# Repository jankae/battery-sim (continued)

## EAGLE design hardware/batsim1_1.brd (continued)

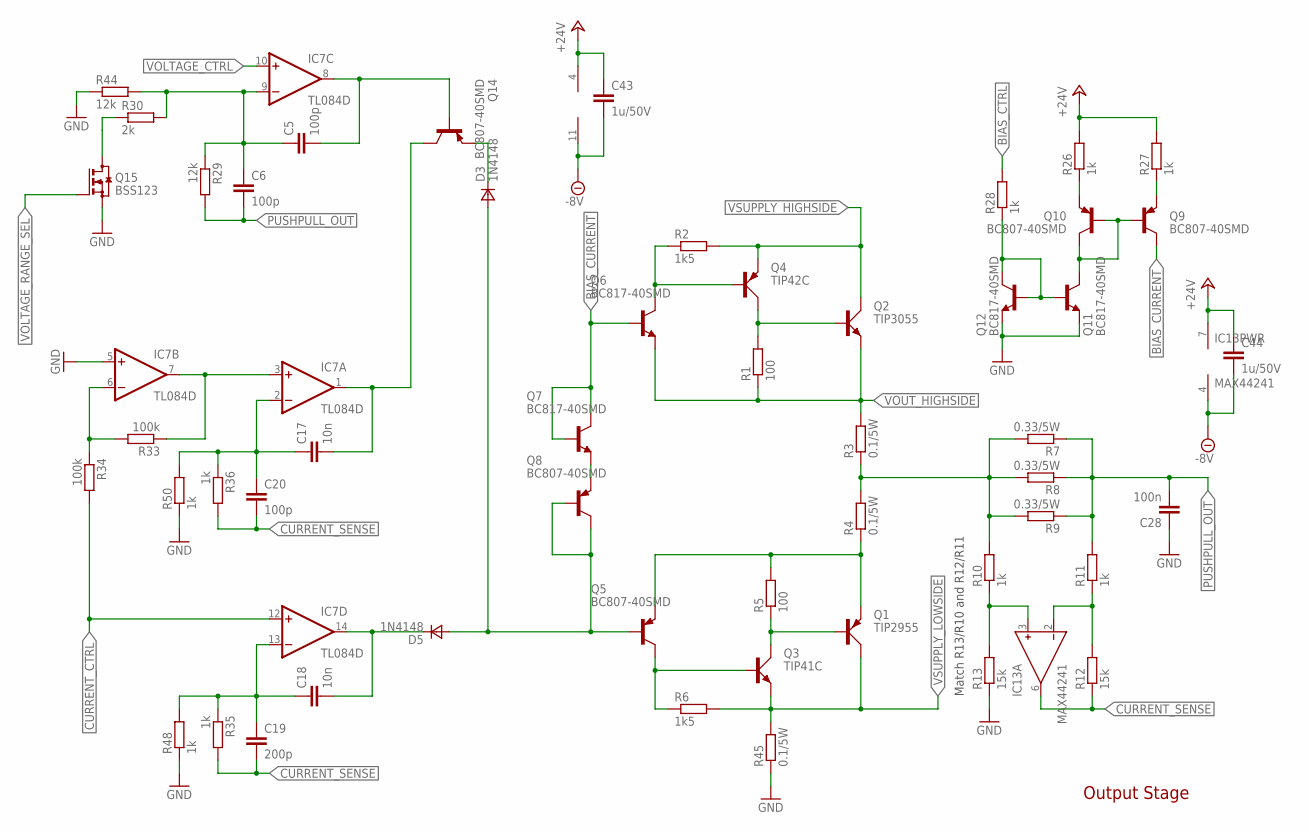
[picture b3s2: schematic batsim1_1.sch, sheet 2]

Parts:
C5, C6, C20: 100p; C0603
C17, C18: 10n; C0603
C19: 200p; C0603
C28: 100n; C1206
C43, C44: 1u/50V; C0603
D3, D5: 1N4148; SOD323
IC7: TL084D; SO14
IC13: MAX44241; UMAX8
Q1: TIP2955; TOP3AV
Q2: TIP3055; TOP3AV
Q3: TIP41C; TO220AV
Q4: TIP42C; TO220AV
Q5, Q8, Q9, Q10, Q14: BC807-40SMD; SOT23-BEC
Q6, Q7, Q11, Q12: BC817-40SMD; SOT23-BEC
Q15: BSS123; SOT23
R1, R5: 100; R0603
R2, R6: 1k5; R0603
R3, R4, R45: 0.1/5W; 5WAXIAL
R7, R8, R9: 0.33/5W; 5WAXIAL
R10, R11, R26, R27, R28, R35, R36, R48, R50: 1k; R0603
R12, R13: 15k; R0603
R29, R44: 12k; R0603
R30: 2k; R0603
R33, R34: 100k; R0603

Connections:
+24V: C43.1, C44.1, IC7.4 (V+), IC13.7 (V+), R26.2, R27.2; also elsewhere on the board
-8V: C43.2, C44.2, IC7.11 (V-), IC13.4 (V-); also elsewhere on the board
BIAS_CTRL: R28.2; also elsewhere on the board
BIAS_CURRENT: Q6.B, Q7.B, Q7.C, Q9.C
CURRENT_CTRL: IC7.12 (+IN), R34.2; also elsewhere on the board
CURRENT_SENSE: C19.2, C20.2, IC13.6 (OUT), R12.1, R35.2, R36.2; also elsewhere on the board
GND: C28.1, IC7.5 (+IN), Q11.E, Q12.E, Q15.2 (S), R13.1, R44.1, R45.1, R48.1, R50.1; also elsewhere on the board
unnamed: Q15.3 (D), R30.1
unnamed: Q2.B, Q4.C, R1.2
unnamed: Q4.B, Q6.C, R2.1
unnamed: R3.1, R4.2, R7.2, R8.2, R9.2, R10.2
unnamed: Q1.E, Q5.E, R4.1, R5.2
unnamed: Q1.B, Q3.C, R5.1
unnamed: Q3.B, Q5.C, R6.1
unnamed: Q7.E, Q8.E
unnamed: D3.1 (C), Q14.E
unnamed: IC13.3 (IN+), R10.1, R13.2
unnamed: IC13.2 (IN-), R11.1, R12.2
unnamed: Q9.B, Q10.B, Q10.C, Q11.C
unnamed: Q11.B, Q12.B, Q12.C, R28.1
unnamed: Q10.E, R26.1
unnamed: Q9.E, R27.1
unnamed: C5.2, IC7.8 (OUT), Q14.B
unnamed: IC7.6 (-IN), R33.2, R34.1
unnamed: IC7.3 (+IN), IC7.7 (OUT), R33.1
unnamed: C18.2, D5.1 (C), IC7.14 (OUT)
unnamed: C18.1, C19.1, IC7.13 (-IN), R35.1, R48.2
unnamed: C17.2, IC7.1 (OUT), Q14.C
unnamed: C17.1, C20.1, IC7.2 (-IN), R36.1, R50.2
PUSHPULL_CTRL: D3.2 (A), D5.2 (A), Q5.B, Q8.B, Q8.C
PUSHPULL_OUT: C6.2, C28.2, R7.1, R8.1, R9.1, R11.2, R29.2; also elsewhere on the board
VOLTAGE_CTRL: IC7.10 (+IN); also elsewhere on the board
VOLTAGE_FEEDBACK: C5.1, C6.1, IC7.9 (-IN), R29.1, R30.2, R44.2
VOLTAGE_RANGE_SEL: Q15.1 (G); also elsewhere on the board
VOUT_HIGHSIDE: Q2.E, Q6.E, R1.1, R3.2; also elsewhere on the board
VSUPPLY_HIGHSIDE: Q2.C, Q4.E, R2.2; also elsewhere on the board
VSUPPLY_LOWSIDE: Q1.C, Q3.E, R6.2, R45.2; also elsewhere on the board

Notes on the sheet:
Match R13/R10 and R12/R11
Output Stage

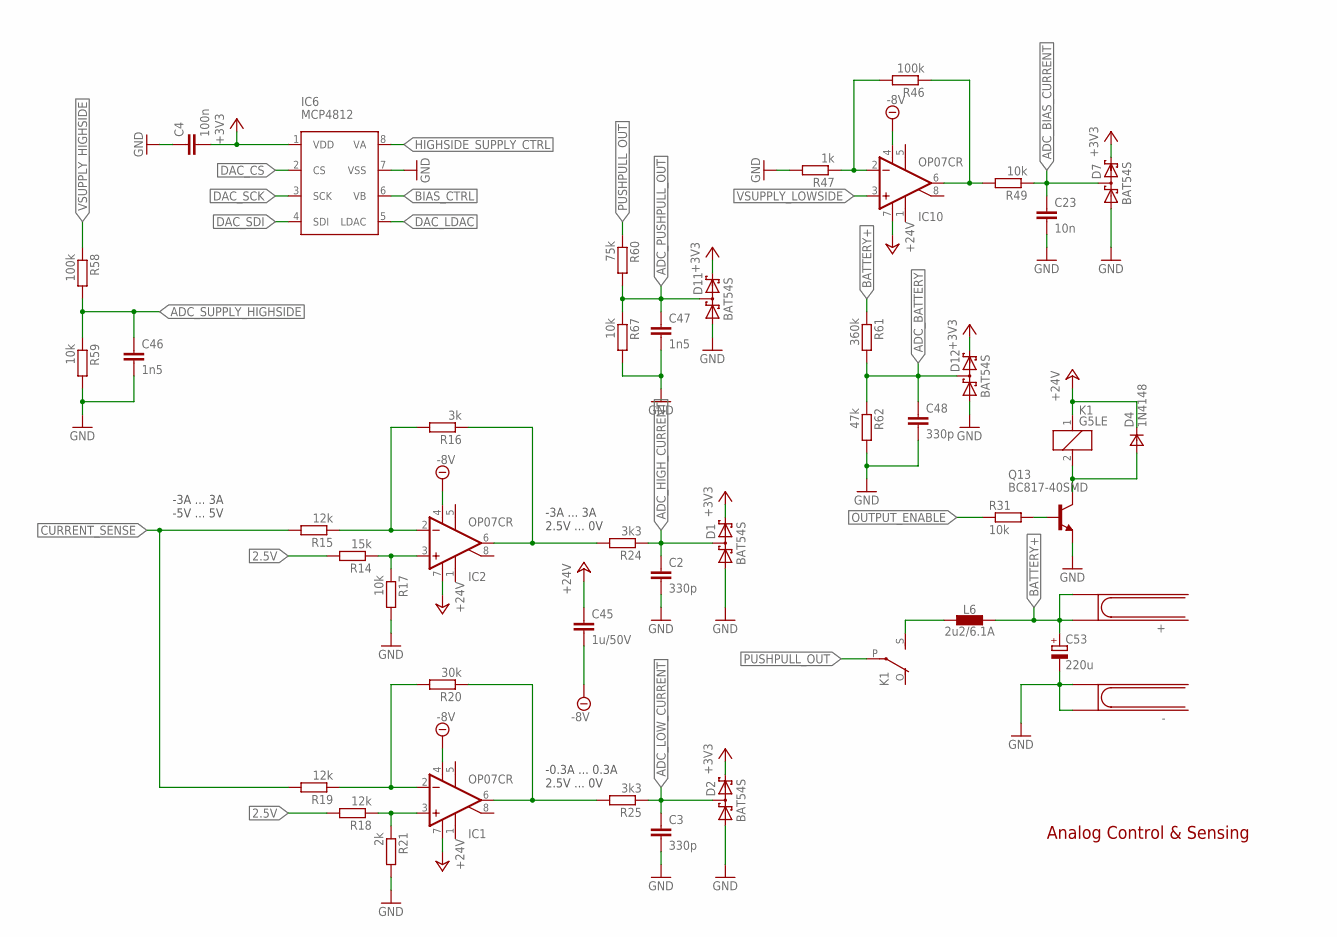
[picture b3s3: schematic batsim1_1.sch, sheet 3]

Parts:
+: 4MMJACK
-: 4MMJACK
C2, C3, C48: 330p; C0603
C4: 100n; C0603
C23: 10n; C0603
C45: 1u/50V; C0603
C46, C47: 1n5; C0603
C53: 220u; E5-10,5
D1, D2, D7, D11, D12: BAT54S; SOT23
D4: 1N4148; SOD323
IC1, IC2, IC10: OP07CR; SO08
IC6: MCP4812; SO08
K1: G5LE
L6: 2u2/6.1A; L_NR60XX
Q13: BC817-40SMD; SOT23-BEC
R14: 15k; R0603
R15, R18, R19: 12k; R0603
R16: 3k; R0603
R17, R31, R49, R59, R67: 10k; R0603
R20: 30k; R0603
R21: 2k; R0603
R24, R25: 3k3; R0603
R46, R58: 100k; R0603
R47: 1k; R0603
R60: 75k; R0603
R61: 360k; R0603
R62: 47k; R0603

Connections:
2.5V: R14.2, R18.2; also elsewhere on the board
+3V3: C4.2, D1.2 (C2), D2.2 (C2), D7.2 (C2), D11.2 (C2), D12.2 (C2), IC6.1 (VDD); also elsewhere on the board
+24V: C45.1, D4.1 (C), IC1.7 (V+), IC2.7 (V+), IC10.7 (V+), K1.1; also elsewhere on the board
-8V: C45.2, IC1.4 (V-), IC2.4 (V-), IC10.4 (V-); also elsewhere on the board
ADC_BATTERY: C48.1, D12.3 (C1A2), R61.2, R62.1; also elsewhere on the board
ADC_BIAS_CURRENT: C23.1, D7.3 (C1A2), R49.1; also elsewhere on the board
ADC_HIGH_CURRENT: C2.1, D1.3 (C1A2), R24.1; also elsewhere on the board
ADC_LOW_CURRENT: C3.1, D2.3 (C1A2), R25.1; also elsewhere on the board
ADC_PUSHPULL_OUT: C47.1, D11.3 (C1A2), R60.2, R67.1; also elsewhere on the board
ADC_SUPPLY_HIGHSIDE: C46.1, R58.2, R59.1; also elsewhere on the board
BATTERY+: +.1@1 (1), +.1@2 (2), C53.+, L6.2, R61.1
BIAS_CTRL: IC6.6 (VB); also elsewhere on the board
CURRENT_SENSE: R15.2, R19.2; also elsewhere on the board
DAC_CS: IC6.2 (CS); also elsewhere on the board
DAC_LDAC: IC6.5 (LDAC); also elsewhere on the board
DAC_SCK: IC6.3 (SCK); also elsewhere on the board
DAC_SDI: IC6.4 (SDI); also elsewhere on the board
GND: -.1@1 (1), -.1@2 (2), C2.2, C3.2, C4.1, C23.2, C46.2, C47.2, C48.2, C53.-, D1.1 (A1), D2.1 (A1), D7.1 (A1), D11.1 (A1), D12.1 (A1), IC6.7 (VSS), Q13.E, R17.2, R21.2, R47.2, R59.2, R62.2, R67.2; also elsewhere on the board
HIGHSIDE_SUPPLY_CTRL: IC6.8 (VA); also elsewhere on the board
unnamed: IC10.2 (-IN), R46.2, R47.1
unnamed: IC10.6 (OUT), R46.1, R49.2
unnamed: D4.2 (A), K1.2, Q13.C
unnamed: IC2.3 (+IN), R14.1, R17.1
unnamed: IC2.2 (-IN), R15.1, R16.2
unnamed: IC2.6 (OUT), R16.1, R24.2
unnamed: IC1.3 (+IN), R18.1, R21.1
unnamed: IC1.2 (-IN), R19.1, R20.2
unnamed: IC1.6 (OUT), R20.1, R25.2
unnamed: Q13.B, R31.2
unnamed: K1.S, L6.1
OUTPUT_ENABLE: R31.1; also elsewhere on the board
PUSHPULL_OUT: K1.P, R60.1; also elsewhere on the board
VSUPPLY_HIGHSIDE: R58.1; also elsewhere on the board
VSUPPLY_LOWSIDE: IC10.3 (+IN); also elsewhere on the board

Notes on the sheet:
-3A ... 3A -5V ... 5V
-3A ... 3A 2.5V ... 0V
-0.3A ... 0.3A 2.5V ... 0V
Analog Control & Sensing

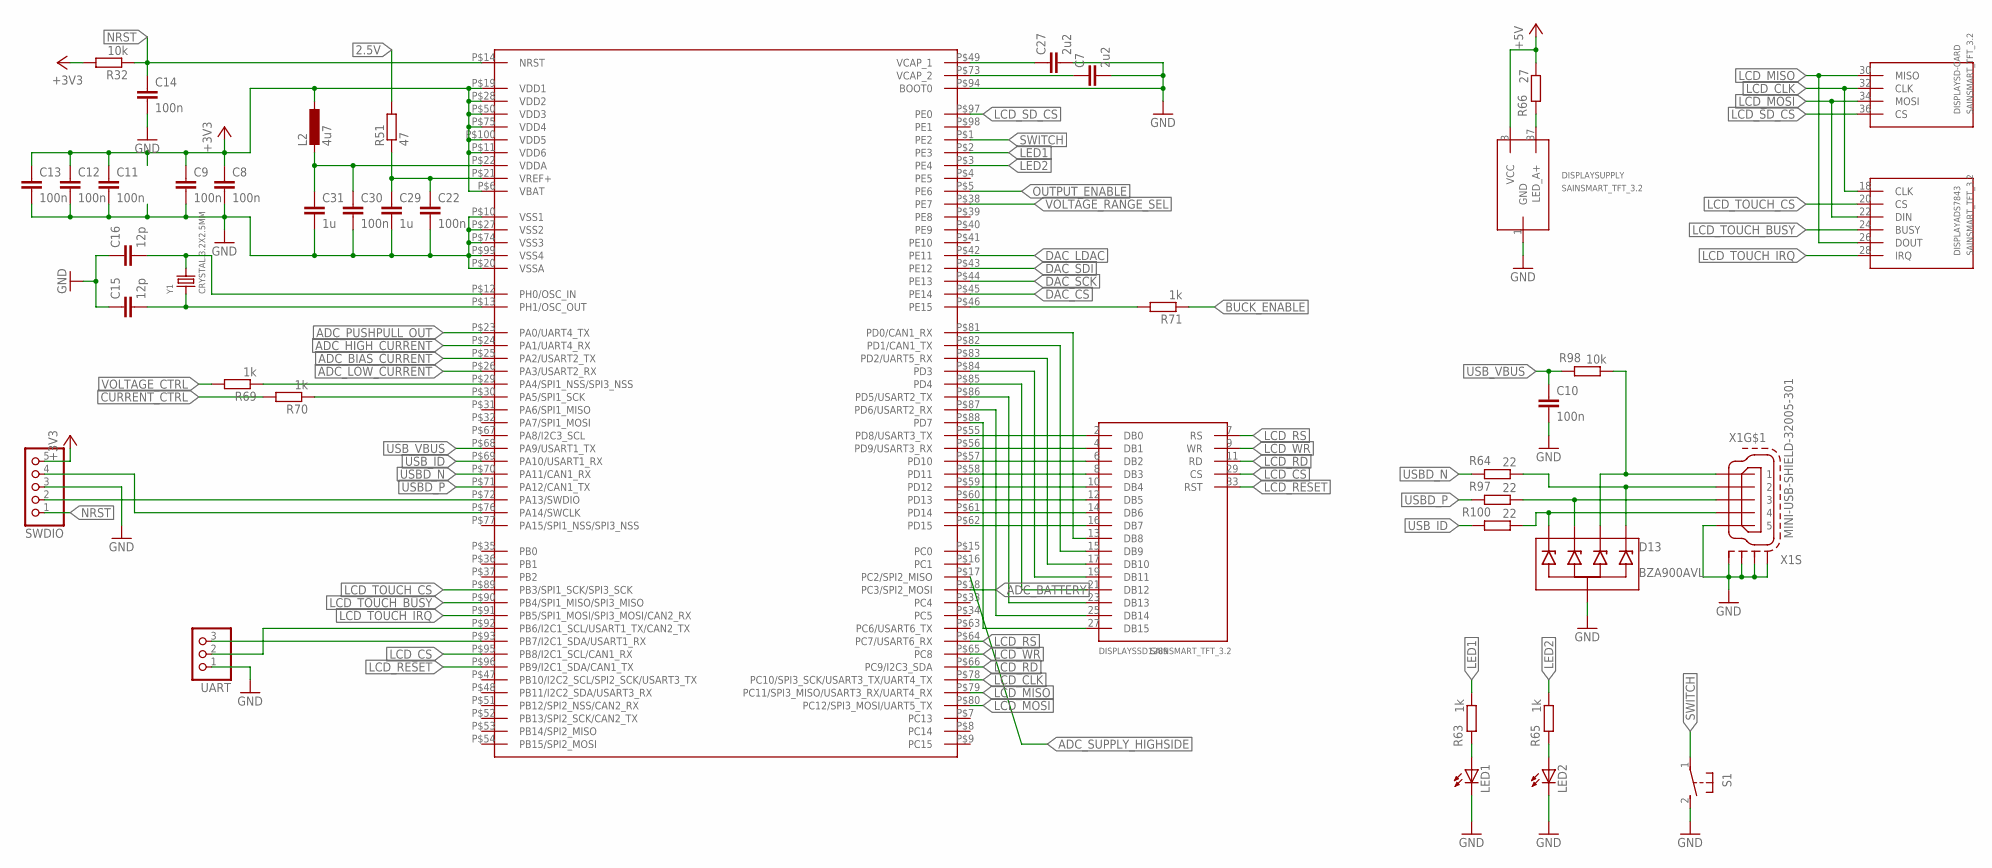
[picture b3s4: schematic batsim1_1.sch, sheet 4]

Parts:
C7, C27: 2u2; C1206
C8, C9, C11, C12, C13, C14, C22, C30: 100n; C0603
C10: 100n; C0603K
C15, C16: 12p; C0603
C29, C31: 1u; C0603
D13: BZA900AVL; SOT-665
DISPLAY: SAINSMART_TFT_3.2
L2: 4u7; L2012C
LED1, LED2: LEDCHIP-LED0603; CHIP-LED0603
R32, R98: 10k; R0603
R51: 47; R0603
R63, R65, R69, R70, R71: 1k; R0603
R64, R97, R100: 22; R0603
R66: 27; R0603
S1: 31-XX; B3F-31XX
SWDIO: PINHD-1X5; 1X05
U$1: STM32F407X100; LQFP100_14
UART: PINHD-1X3; 1X03
X1: MINI-USB-SHIELD-32005-301; 32005-301
Y1: CRYSTAL.3.2X2.5MM; 3.2X2.5MM

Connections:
2.5V: R51.2; also elsewhere on the board
+3V3: C8.1, C9.1, C11.1, C12.1, C13.1, L2.1, R32.2, SWDIO.5, U$1.P$6 (VBAT), U$1.P$11 (VDD6), U$1.P$19 (VDD1), U$1.P$28 (VDD2), U$1.P$50 (VDD3), U$1.P$75 (VDD4), U$1.P$100 (VDD5); also elsewhere on the board
+5V: DISPLAY.3 (VCC), R66.1; also elsewhere on the board
ADC_BATTERY: U$1.P$18 (PC3/SPI2_MOSI); also elsewhere on the board
ADC_BIAS_CURRENT: U$1.P$25 (PA2/USART2_TX); also elsewhere on the board
ADC_HIGH_CURRENT: U$1.P$24 (PA1/UART4_RX); also elsewhere on the board
ADC_LOW_CURRENT: U$1.P$26 (PA3/USART2_RX); also elsewhere on the board
ADC_PUSHPULL_OUT: U$1.P$23 (PA0/UART4_TX); also elsewhere on the board
ADC_SUPPLY_HIGHSIDE: U$1.P$17 (PC2/SPI2_MISO); also elsewhere on the board
BUCK_ENABLE: R71.1; also elsewhere on the board
CURRENT_CTRL: R70.2; also elsewhere on the board
DAC_CS: U$1.P$45 (PE14); also elsewhere on the board
DAC_LDAC: U$1.P$42 (PE11); also elsewhere on the board
DAC_SCK: U$1.P$44 (PE13); also elsewhere on the board
DAC_SDI: U$1.P$43 (PE12); also elsewhere on the board
GND: C7.2, C8.2, C9.2, C10.2, C11.2, C12.2, C13.2, C14.2, C15.1, C16.1, C22.2, C27.2, C29.2, C30.2, C31.2, D13.2 (COM), DISPLAY.1 (GND), LED1.C, LED2.C, S1.2 (S), SWDIO.3, U$1.P$10 (VSS1), U$1.P$20 (VSSA), U$1.P$27 (VSS2), U$1.P$74 (VSS3), U$1.P$94 (BOOT0), U$1.P$99 (VSS4), UART.1, X1.5, X1.M1 (S1), X1.M2 (S2), X1.M3 (S3), X1.M4 (S4); also elsewhere on the board
LCD_CLK: DISPLAY.18 (CLK), DISPLAY.32 (CLK), U$1.P$78 (PC10/SPI3_SCK/USART3_TX/UART4_TX)
LCD_CS: DISPLAY.29 (CS), U$1.P$95 (PB8/I2C1_SCL/CAN1_RX)
LCD_MISO: DISPLAY.26 (DOUT), DISPLAY.30 (MISO), U$1.P$79 (PC11/SPI3_MISO/USART3_RX/UART4_RX)
LCD_MOSI: DISPLAY.22 (DIN), DISPLAY.34 (MOSI), U$1.P$80 (PC12/SPI3_MOSI/UART5_TX)
LCD_RD: DISPLAY.11 (RD), U$1.P$66 (PC9/I2C3_SDA)
LCD_RESET: DISPLAY.33 (RST), U$1.P$96 (PB9/I2C1_SDA/CAN1_TX)
LCD_RS: DISPLAY.7 (RS), U$1.P$64 (PC7/USART6_RX)
LCD_SD_CS: DISPLAY.36 (CS), U$1.P$97 (PE0)
LCD_TOUCH_BUSY: DISPLAY.24 (BUSY), U$1.P$90 (PB4/SPI1_MISO/SPI3_MISO)
LCD_TOUCH_CS: DISPLAY.20 (CS), U$1.P$89 (PB3/SPI1_SCK/SPI3_SCK)
LCD_TOUCH_IRQ: DISPLAY.28 (IRQ), U$1.P$91 (PB5/SPI1_MOSI/SPI3_MOSI/CAN2_RX)
LCD_WR: DISPLAY.9 (WR), U$1.P$65 (PC8)
LED1: R63.1, U$1.P$2 (PE3)
LED2: R65.1, U$1.P$3 (PE4)
unnamed: SWDIO.4, U$1.P$76 (PA14/SWCLK)
unnamed: D13.3 (2), R97.1, X1.3
unnamed: C16.2, U$1.P$12 (PH0/OSC_IN), Y1.3 (2)
unnamed: C15.2, U$1.P$13 (PH1/OSC_OUT), Y1.1
unnamed: SWDIO.2, U$1.P$72 (PA13/SWDIO)
unnamed: C27.1, U$1.P$49 (VCAP_1)
unnamed: C7.1, U$1.P$73 (VCAP_2)
unnamed: D13.5 (4), R64.1, X1.2
unnamed: D13.4 (3), R98.1, X1.1
unnamed: D13.1, R100.1, X1.4
unnamed: DISPLAY.37 (LED_A+), R66.2
unnamed: DISPLAY.2 (DB0), U$1.P$55 (PD8/USART3_TX)
unnamed: DISPLAY.4 (DB1), U$1.P$56 (PD9/USART3_RX)
unnamed: DISPLAY.6 (DB2), U$1.P$57 (PD10)
unnamed: DISPLAY.8 (DB3), U$1.P$58 (PD11)
unnamed: DISPLAY.10 (DB4), U$1.P$59 (PD12)
unnamed: DISPLAY.12 (DB5), U$1.P$60 (PD13)
unnamed: DISPLAY.14 (DB6), U$1.P$61 (PD14)
unnamed: DISPLAY.16 (DB7), U$1.P$62 (PD15)
unnamed: LED1.A, R63.2
unnamed: LED2.A, R65.2
unnamed: R69.1, U$1.P$29 (PA4/SPI1_NSS/SPI3_NSS)
unnamed: DISPLAY.19 (DB11), U$1.P$84 (PD3)
unnamed: DISPLAY.17 (DB10), U$1.P$83 (PD2/UART5_RX)
unnamed: DISPLAY.15 (DB9), U$1.P$82 (PD1/CAN1_TX)
unnamed: DISPLAY.13 (DB8), U$1.P$81 (PD0/CAN1_RX)
unnamed: R70.1, U$1.P$30 (PA5/SPI1_SCK)
unnamed: R71.2, U$1.P$46 (PE15)
unnamed: DISPLAY.21 (DB12), U$1.P$85 (PD4)
unnamed: DISPLAY.23 (DB13), U$1.P$86 (PD5/USART2_TX)
unnamed: DISPLAY.25 (DB14), U$1.P$87 (PD6/USART2_RX)
unnamed: DISPLAY.27 (DB15), U$1.P$88 (PD7)
NRST: C14.1, R32.1, SWDIO.1, U$1.P$14 (NRST)
OUTPUT_ENABLE: U$1.P$5 (PE6); also elsewhere on the board
RX: U$1.P$93 (PB7/I2C1_SDA/USART1_RX), UART.3
SWITCH: S1.1, U$1.P$1 (PE2)
TX: U$1.P$92 (PB6/I2C1_SCL/USART1_TX/CAN2_TX), UART.2
USBD_N: R64.2, U$1.P$70 (PA11/CAN1_RX)
USBD_P: R97.2, U$1.P$71 (PA12/CAN1_TX)
USB_ID: R100.2, U$1.P$69 (PA10/USART1_RX)
USB_VBUS: C10.1, R98.2, U$1.P$68 (PA9/USART1_TX)
VDDA: C30.1, C31.1, L2.2, U$1.P$22 (VDDA); also elsewhere on the board
VOLTAGE_CTRL: R69.2; also elsewhere on the board
VOLTAGE_RANGE_SEL: U$1.P$38 (PE7); also elsewhere on the board
VREF: C22.1, C29.1, R51.1, U$1.P$21 (VREF+)

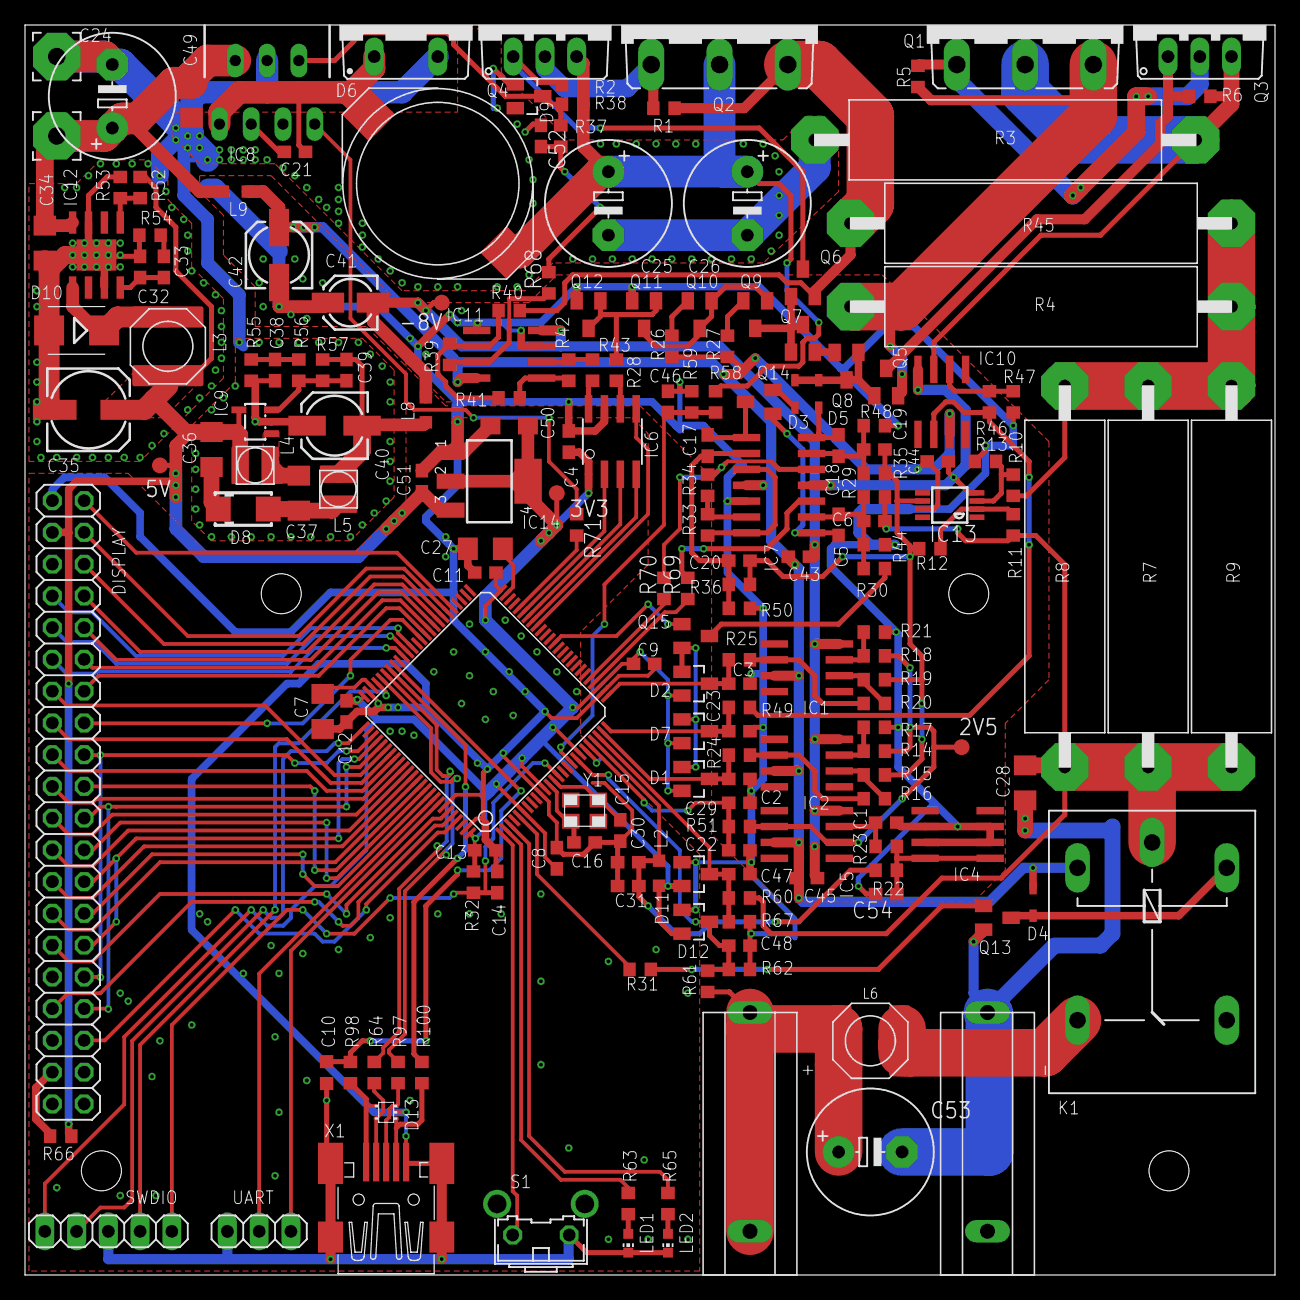
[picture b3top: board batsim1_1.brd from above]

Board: 2 copper layers, 100.0 x 100.0 mm, 195 parts (0 on the bottom side), 141 nets.

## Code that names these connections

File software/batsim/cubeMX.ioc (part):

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Mcu.Name=STM32F103V(C-D-E)Tx
Mcu.Package=LQFP100
Mcu.UserName=STM32F103VETx
PA10.Mode=Asynchronous
PA10.Signal=USART1_RX
PA11.Mode=Device
PA11.Signal=USB_DM
PA12.Mode=Device
PA12.Signal=USB_DP
PA13.Mode=Serial_Wire
PA13.Signal=SYS_JTMS-SWDIO
PA14.Mode=Serial_Wire
PA14.Signal=SYS_JTCK-SWCLK
PA15.GPIOParameters=GPIO_PuPd
PA15.GPIO_PuPd=GPIO_PULLUP
PA15.Signal=GPIO_Input
PA5.Mode=Full_Duplex_Master
PA5.Signal=SPI1_SCK
PA6.GPIOParameters=GPIO_PuPd
PA6.GPIO_PuPd=GPIO_PULLUP
PA6.Mode=Full_Duplex_Master
PA6.Signal=SPI1_MISO
PA7.Mode=Full_Duplex_Master
PA7.Signal=SPI1_MOSI
PA8.Signal=GPIO_Output
PA9.Mode=Asynchronous
PA9.Signal=USART1_TX
PB0.Signal=ADCx_IN8
PB1.Signal=GPIO_Output
PB14.GPIOParameters=GPIO_Speed
PB14.GPIO_Speed=GPIO_SPEED_FREQ_HIGH
PB14.Signal=GPIO_Output
PB15.GPIOParameters=GPIO_Speed
PB15.GPIO_Speed=GPIO_SPEED_FREQ_HIGH
PB15.Signal=GPIO_Output
PB3.Mode=Full_Duplex_Master
PB3.Signal=SPI3_SCK
PB4.GPIOParameters=GPIO_PuPd
PB4.GPIO_PuPd=GPIO_PULLUP
PB4.Mode=Full_Duplex_Master
PB4.Signal=SPI3_MISO
PB5.Mode=Full_Duplex_Master
PB5.Signal=SPI3_MOSI
PB6.GPIOParameters=GPIO_Speed,PinState
PB6.GPIO_Speed=GPIO_SPEED_FREQ_HIGH
PB6.PinState=GPIO_PIN_SET
PB6.Signal=GPIO_Output
PB7.GPIOParameters=GPIO_Speed,PinState
PB7.GPIO_Speed=GPIO_SPEED_FREQ_HIGH
PB7.PinState=GPIO_PIN_SET
PB7.Signal=GPIO_Output
PB8.GPIOParameters=GPIO_PuPd
PB8.GPIO_PuPd=GPIO_PULLUP
PB8.Signal=GPIO_Input
PB9.GPIOParameters=GPIO_Speed
PB9.GPIO_Speed=GPIO_SPEED_FREQ_HIGH
PB9.Signal=GPIO_Output
PC10.Signal=GPIO_Output
PC11.Signal=GPIO_Output
PC12.GPIOParameters=GPIO_PuPd
PC12.GPIO_PuPd=GPIO_PULLUP
PC12.Signal=GPIO_Input
PC14-OSC32_IN.GPIOParameters=GPIO_PuPd
PC14-OSC32_IN.GPIO_PuPd=GPIO_PULLUP
PC14-OSC32_IN.Signal=GPIO_Input
PC6.GPIOParameters=GPIO_Speed
PC6.GPIO_Speed=GPIO_SPEED_FREQ_HIGH
PC6.Signal=GPIO_Output
PC7.Signal=GPIO_Output
PC9.Signal=GPIO_Output
PD0.GPIOParameters=GPIO_Speed,PinState
PD0.GPIO_Speed=GPIO_SPEED_FREQ_HIGH
PD0.PinState=GPIO_PIN_RESET
PD0.Signal=GPIO_Output
PD1.GPIOParameters=GPIO_Speed
PD1.GPIO_Speed=GPIO_SPEED_FREQ_HIGH
PD1.Signal=GPIO_Output
PD10.GPIOParameters=GPIO_Speed
PD10.GPIO_Speed=GPIO_SPEED_FREQ_HIGH
PD10.Signal=GPIO_Output
PD11.GPIOParameters=GPIO_Speed
PD11.GPIO_Speed=GPIO_SPEED_FREQ_HIGH
PD11.Signal=GPIO_Output
PD12.GPIOParameters=GPIO_Speed
PD12.GPIO_Speed=GPIO_SPEED_FREQ_HIGH
PD12.Signal=GPIO_Output
PD13.GPIOParameters=GPIO_Speed
PD13.GPIO_Speed=GPIO_SPEED_FREQ_HIGH
PD13.Signal=GPIO_Output
PD14.GPIOParameters=GPIO_Speed
PD14.GPIO_Speed=GPIO_SPEED_FREQ_HIGH
PD14.Signal=GPIO_Output
PD15.GPIOParameters=GPIO_Speed
PD15.GPIO_Speed=GPIO_SPEED_FREQ_HIGH
PD15.Signal=GPIO_Output
PD2.GPIOParameters=GPIO_Speed
PD2.GPIO_Speed=GPIO_SPEED_FREQ_HIGH
PD2.Signal=GPIO_Output
PD3.GPIOParameters=GPIO_Speed
PD3.GPIO_Speed=GPIO_SPEED_FREQ_HIGH
PD3.Signal=GPIO_Output
PD4.GPIOParameters=GPIO_Speed
PD4.GPIO_Speed=GPIO_SPEED_FREQ_HIGH
PD4.Signal=GPIO_Output
PD5.GPIOParameters=GPIO_Speed
PD5.GPIO_Speed=GPIO_SPEED_FREQ_HIGH
PD5.Signal=GPIO_Output
PD6.GPIOParameters=GPIO_Speed
PD6.GPIO_Speed=GPIO_SPEED_FREQ_HIGH
PD6.Signal=GPIO_Output
PD7.GPIOParameters=GPIO_Speed
PD7.GPIO_Speed=GPIO_SPEED_FREQ_HIGH
PD7.Signal=GPIO_Output
PD8.GPIOParameters=GPIO_Speed
PD8.GPIO_Speed=GPIO_SPEED_FREQ_HIGH
PD8.Signal=GPIO_Output
PD9.GPIOParameters=GPIO_Speed
PD9.GPIO_Speed=GPIO_SPEED_FREQ_HIGH
PD9.Signal=GPIO_Output
PE0.GPIOParameters=GPIO_Speed
PE0.GPIO_Speed=GPIO_SPEED_FREQ_HIGH
PE0.Signal=GPIO_Output
PE1.GPIOParameters=GPIO_PuPd
PE1.GPIO_PuPd=GPIO_PULLUP
PE1.Signal=GPIO_Input
PE2.GPIOParameters=GPIO_PuPd
PE2.GPIO_PuPd=GPIO_PULLUP
PE2.Signal=GPIO_Input
PE3.GPIOParameters=GPIO_PuPd
PE3.GPIO_PuPd=GPIO_PULLUP
PE3.Signal=GPIO_Input
RCC.SYSCLKFreq_VALUE=72000000
RCC.SYSCLKSource=RCC_SYSCLKSOURCE_PLLCLK
board=cubeMX

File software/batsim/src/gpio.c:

/**
  ******************************************************************************
  * File Name          : gpio.c
  * Description        : This file provides code for the configuration
  *                      of all used GPIO pins.
  ******************************************************************************
  *
  * COPYRIGHT(c) 2017 STMicroelectronics
  *
  * Redistribution and use in source and binary forms, with or without modification,
  * are permitted provided that the following conditions are met:
  *   1. Redistributions of source code must retain the above copyright notice,
  *      this list of conditions and the following disclaimer.
  *   2. Redistributions in binary form must reproduce the above copyright notice,
  *      this list of conditions and the following disclaimer in the documentation
  *      and/or other materials provided with the distribution.
  *   3. Neither the name of STMicroelectronics nor the names of its contributors
  *      may be used to endorse or promote products derived from this software
  *      without specific prior written permission.
  *
  * THIS SOFTWARE IS PROVIDED BY THE COPYRIGHT HOLDERS AND CONTRIBUTORS "AS IS"
  * AND ANY EXPRESS OR IMPLIED WARRANTIES, INCLUDING, BUT NOT LIMITED TO, THE
  * IMPLIED WARRANTIES OF MERCHANTABILITY AND FITNESS FOR A PARTICULAR PURPOSE ARE
  * DISCLAIMED. IN NO EVENT SHALL THE COPYRIGHT HOLDER OR CONTRIBUTORS BE LIABLE
  * FOR ANY DIRECT, INDIRECT, INCIDENTAL, SPECIAL, EXEMPLARY, OR CONSEQUENTIAL
  * DAMAGES (INCLUDING, BUT NOT LIMITED TO, PROCUREMENT OF SUBSTITUTE GOODS OR
  * SERVICES; LOSS OF USE, DATA, OR PROFITS; OR BUSINESS INTERRUPTION) HOWEVER
  * CAUSED AND ON ANY THEORY OF LIABILITY, WHETHER IN CONTRACT, STRICT LIABILITY,
  * OR TORT (INCLUDING NEGLIGENCE OR OTHERWISE) ARISING IN ANY WAY OUT OF THE USE
  * OF THIS SOFTWARE, EVEN IF ADVISED OF THE POSSIBILITY OF SUCH DAMAGE.
  *
  ******************************************************************************
  */

/* Includes ------------------------------------------------------------------*/
#include "gpio.h"
/* USER CODE BEGIN 0 */

/* USER CODE END 0 */

/*----------------------------------------------------------------------------*/
/* Configure GPIO                                                             */
/*----------------------------------------------------------------------------*/
/* USER CODE BEGIN 1 */

/* USER CODE END 1 */

/** Configure pins as 
        * Analog 
        * Input 
        * Output
        * EVENT_OUT
        * EXTI
*/
void MX_GPIO_Init(void)
{

  GPIO_InitTypeDef GPIO_InitStruct;

  /* GPIO Ports Clock Enable */
  __HAL_RCC_GPIOE_CLK_ENABLE();
  __HAL_RCC_GPIOH_CLK_ENABLE();
  __HAL_RCC_GPIOC_CLK_ENABLE();
  __HAL_RCC_GPIOA_CLK_ENABLE();
  __HAL_RCC_GPIOD_CLK_ENABLE();
  __HAL_RCC_GPIOB_CLK_ENABLE();

  /*Configure GPIO pin Output Level */
  HAL_GPIO_WritePin(GPIOE, GPIO_PIN_6|GPIO_PIN_7|GPIO_PIN_11|GPIO_PIN_12
                          |GPIO_PIN_13|GPIO_PIN_14|GPIO_PIN_15, GPIO_PIN_RESET);

  /*Configure GPIO pin Output Level */
  HAL_GPIO_WritePin(GPIOD, GPIO_PIN_8|GPIO_PIN_9|GPIO_PIN_10|GPIO_PIN_11
                          |GPIO_PIN_12|GPIO_PIN_13|GPIO_PIN_14|GPIO_PIN_15
                          |GPIO_PIN_0|GPIO_PIN_1|GPIO_PIN_2|GPIO_PIN_3
                          |GPIO_PIN_4|GPIO_PIN_5|GPIO_PIN_6|GPIO_PIN_7, GPIO_PIN_RESET);

  /*Configure GPIO pin Output Level */
  HAL_GPIO_WritePin(GPIOC, GPIO_PIN_7|GPIO_PIN_8|GPIO_PIN_9|GPIO_PIN_10
                          |GPIO_PIN_12, GPIO_PIN_RESET);

  /*Configure GPIO pin Output Level */
  HAL_GPIO_WritePin(GPIOB, GPIO_PIN_3|GPIO_PIN_8|GPIO_PIN_9, GPIO_PIN_RESET);

  /*Configure GPIO pins : PE6 PE7 PE15 */
  GPIO_InitStruct.Pin = GPIO_PIN_6|GPIO_PIN_7|GPIO_PIN_15;
  GPIO_InitStruct.Mode = GPIO_MODE_OUTPUT_PP;
  GPIO_InitStruct.Pull = GPIO_NOPULL;
  GPIO_InitStruct.Speed = GPIO_SPEED_FREQ_LOW;
  HAL_GPIO_Init(GPIOE, &GPIO_InitStruct);

  /*Configure GPIO pins : PE11 PE12 PE13 PE14 */
  GPIO_InitStruct.Pin = GPIO_PIN_11|GPIO_PIN_12|GPIO_PIN_13|GPIO_PIN_14;
  GPIO_InitStruct.Mode = GPIO_MODE_OUTPUT_PP;
  GPIO_InitStruct.Pull = GPIO_NOPULL;
  GPIO_InitStruct.Speed = GPIO_SPEED_FREQ_MEDIUM;
  HAL_GPIO_Init(GPIOE, &GPIO_InitStruct);

  /*Configure GPIO pins : PD8 PD9 PD10 PD11
                           PD12 PD13 PD14 PD15
                           PD0 PD1 PD2 PD3
                           PD4 PD5 PD6 PD7 */
  GPIO_InitStruct.Pin = GPIO_PIN_8|GPIO_PIN_9|GPIO_PIN_10|GPIO_PIN_11
                          |GPIO_PIN_12|GPIO_PIN_13|GPIO_PIN_14|GPIO_PIN_15
                          |GPIO_PIN_0|GPIO_PIN_1|GPIO_PIN_2|GPIO_PIN_3
                          |GPIO_PIN_4|GPIO_PIN_5|GPIO_PIN_6|GPIO_PIN_7;
  GPIO_InitStruct.Mode = GPIO_MODE_OUTPUT_PP;
  GPIO_InitStruct.Pull = GPIO_NOPULL;
  GPIO_InitStruct.Speed = GPIO_SPEED_FREQ_HIGH;
  HAL_GPIO_Init(GPIOD, &GPIO_InitStruct);

  /*Configure GPIO pins : PC7 PC8 PC9 PC10
                           PC12 */
  GPIO_InitStruct.Pin = GPIO_PIN_7|GPIO_PIN_8|GPIO_PIN_9|GPIO_PIN_10
                          |GPIO_PIN_12;
  GPIO_InitStruct.Mode = GPIO_MODE_OUTPUT_PP;
  GPIO_InitStruct.Pull = GPIO_NOPULL;
  GPIO_InitStruct.Speed = GPIO_SPEED_FREQ_HIGH;
  HAL_GPIO_Init(GPIOC, &GPIO_InitStruct);

  /*Configure GPIO pin : PC11 */
  GPIO_InitStruct.Pin = GPIO_PIN_11;
  GPIO_InitStruct.Mode = GPIO_MODE_INPUT;
  GPIO_InitStruct.Pull = GPIO_PULLUP;
  HAL_GPIO_Init(GPIOC, &GPIO_InitStruct);

  /*Configure GPIO pins : PB3 PB8 PB9 */
  GPIO_InitStruct.Pin = GPIO_PIN_3|GPIO_PIN_8|GPIO_PIN_9;
  GPIO_InitStruct.Mode = GPIO_MODE_OUTPUT_PP;
  GPIO_InitStruct.Pull = GPIO_NOPULL;
  GPIO_InitStruct.Speed = GPIO_SPEED_FREQ_HIGH;
  HAL_GPIO_Init(GPIOB, &GPIO_InitStruct);

  /*Configure GPIO pins : PB4 PB5 */
  GPIO_InitStruct.Pin = GPIO_PIN_4|GPIO_PIN_5;
  GPIO_InitStruct.Mode = GPIO_MODE_INPUT;
  GPIO_InitStruct.Pull = GPIO_PULLUP;
  HAL_GPIO_Init(GPIOB, &GPIO_InitStruct);

}

/* USER CODE BEGIN 2 */

/* USER CODE END 2 */

/**
  * @}
  */

/**
  * @}
  */

/************************ (C) COPYRIGHT STMicroelectronics *****END OF FILE****/

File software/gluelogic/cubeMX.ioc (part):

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Mcu.Name=STM32F030C8Tx
Mcu.Package=LQFP48
Mcu.UserName=STM32F030C8Tx
PA0.Mode=IN0
PA0.Signal=ADC_IN0
PA1.Mode=IN1
PA1.Signal=ADC_IN1
PA15.GPIOParameters=GPIO_Label
PA15.GPIO_Label=OUTPUT_ENABLE
PA15.Signal=GPIO_Output
PA2.Mode=IN2
PA2.Signal=ADC_IN2
PA3.Mode=IN3
PA3.Signal=ADC_IN3
PA4.Mode=IN4
PA4.Signal=ADC_IN4
PA5.Mode=IN5
PA5.Signal=ADC_IN5
PA6.Mode=IN6
PA6.Signal=ADC_IN6
PA7.Mode=IN7
PA7.Signal=ADC_IN7
PB0.Mode=IN8
PB0.Signal=ADC_IN8
PB10.Mode=I2C
PB10.Signal=I2C2_SCL
PB11.Mode=I2C
PB11.Signal=I2C2_SDA
PB13.Mode=Full_Duplex_Slave
PB13.Signal=SPI2_SCK
PB14.Mode=Full_Duplex_Slave
PB14.Signal=SPI2_MISO
PB15.Mode=Full_Duplex_Slave
PB15.Signal=SPI2_MOSI
PB3.Mode=Full_Duplex_Master
PB3.Signal=SPI1_SCK
PB4.Mode=Full_Duplex_Master
PB4.Signal=SPI1_MISO
PB5.Mode=Full_Duplex_Master
PB5.Signal=SPI1_MOSI
PB9.GPIOParameters=GPIO_Label
PB9.GPIO_Label=CS_POT
PB9.Signal=GPIO_Output
PC13.GPIOParameters=GPIO_Label
PC13.GPIO_Label=CS_DAC2
PC13.Signal=GPIO_Output
PC14-OSC32_IN.GPIOParameters=GPIO_Label
PC14-OSC32_IN.GPIO_Label=CS_DAC1
PC14-OSC32_IN.Signal=GPIO_Output
RCC.SYSCLKFreq_VALUE=48000000
RCC.SYSCLKSource=RCC_SYSCLKSOURCE_PLLCLK
board=cubeMX

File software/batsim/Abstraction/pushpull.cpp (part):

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
/* Raw ADC word meanings */
#define ADC_TEMPERATURE			0
#define ADC_BATTERY				1
#define ADC_PUSHPULL_OUT		2
#define ADC_LOW_CURRENT			3
#define ADC_HIGH_CURRENT		4
#define ADC_BIAS_CURRENT		5

const PushPull_Limits_t Limits = {
		minVoltage : 0,
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
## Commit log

2017-03-14 Initial setup
2017-03-14 added USB + basic python display substitute
2017-03-15 First GUI elements
2017-03-15 GUI improvements + new element: window
2017-03-15 window bugs fixed
2017-03-16 redrawing requests improved, prevent unnecessary redrawing of parents
2017-03-16 GUI improvements + input dialog
2017-03-16 GUI element: entry
2017-03-21 Basic desktop functions
2017-03-29 GUI adapted to real display + further improvements
2017-03-29 Touch calibration routine added. TODO: store in FLASH
2017-04-20 gitignore extended
2017-04-20 PCB files
2017-04-21 board update
2017-04-21 PCB markings
2017-04-22 minor PCB changes
2017-04-22 final PCB corrections
2017-04-22 Added gerber files
2017-04-23 gitignore for build files
2017-04-23 template code for gluelogic
2017-04-23 Basic glue logic framework
2017-04-23 Makefile improvements
2017-05-01 Switched to STM32F103, initial Cube-Framework
2017-05-02 some adjustments to Makefile and minor changes to remove build errors
2017-05-02 USB submodule removed (not working anyway) + removed warnings
2017-05-02 Pull-ups on inputs
2017-05-02 Pin changes according to new PCB layout
2017-05-02 Button matrix evaluation module
2017-05-02 Encoder added to button routine
2017-05-02 Touch: switched from software to hardware SPI + missing Cube changes
2017-05-02 FatFs user interface added
2017-05-02 Control access to shared SPI3 via mutex
2017-05-02 display rotated 180 degree
2017-05-18 [gluelogic] SPI synchronisation implemented
2017-05-21 Pictures of partial assembly
2017-05-30 lots of minor changes
2017-05-30 ADC sampling time reduced + Calibration on startup
2017-06-02 Debugging of hardware: selftest passes
2017-06-03 Various fixes, getting the buttons and encoder to work
2017-06-05 Touch: Endiannes-fix and inversion
2017-06-06 Bugfixes, GUI improvements, rudimentary bench supply app
2017-06-06 Config files, ADC improvements, internal Resistance added
2017-06-07 App template, warnings reduced, itemChooser widget
2017-06-08 LFN names, saving/loading presets in supply app
2017-06-08 Charger app started, various minor GUI improvements
2017-06-08 Basic charger completed, again minor GUI improvements
2017-06-10 Output calibration
2017-06-10 minor fixes, stack usage debug message
2017-06-11 Calibration of sink current DAC added
2017-06-11 CubeMX update (needs modification after generating!) + USB CDC device
2017-06-11 got rid off warnings
2017-06-11 Allow entry of mX (still not working for generic unit)
2017-06-12 Info App + temperature monitoring
2017-06-12 Minor hardware + gitignore update
2017-06-12 Removed old hardware files, added USB pullup
2017-06-13 Dedicated folder per app
2017-06-13 Fix: memory leak in textfield widget + some todos deleted
2017-06-22 Graph, Battery simulation, minor other fixes
2017-06-26 Bugfixes + beginning of simulator app
2017-06-26 first battery simulation test
2017-06-30 Simulator GUI improved
2017-07-02 Frontpanel layout changed
2017-07-11 Frontpanel layout
2017-07-11 Beginning of characterisation app
2017-09-14 Name clash fix and other bugs
2017-09-14 CubeMX and makefile update
2017-09-14 .c -> .cpp, adjustments to compile with g++
2017-09-14 Reroute new/delete to FreeRTOS heap
2017-09-14 Revert CubeMX changes for broken SPI (do not regenerate)
2017-09-14 Adjust verbose calibration check
2017-09-15 GUI rewritten in C++
2017-09-15 Using lambdas for simple callback functions
2017-09-15 App descriptions and bugfixes
2017-09-15 App names and description removed from Heap
2017-09-16 CubeMX update, SPI timeout increased, SD card working again
2017-09-16 SD SPI speed increase / some debugging improvements
2017-11-28 Added internal resistance to supply + bugfix on file load
2018-03-31 Added active display area (restricting writes to specific area)
2018-04-01 Navigate and select widgets with arrow buttons
2018-04-04 Changed characterisation app for scope
2018-05-10 Calibration routine extendend
    - Overflow in entry string parsing fixed
    - Additional dialog: unit input (easier user input during calibration)
    - Calibration routine bux fixes/calibrating more ranges
2019-06-24 no migration
2019-06-24 Pictures of finsished device
